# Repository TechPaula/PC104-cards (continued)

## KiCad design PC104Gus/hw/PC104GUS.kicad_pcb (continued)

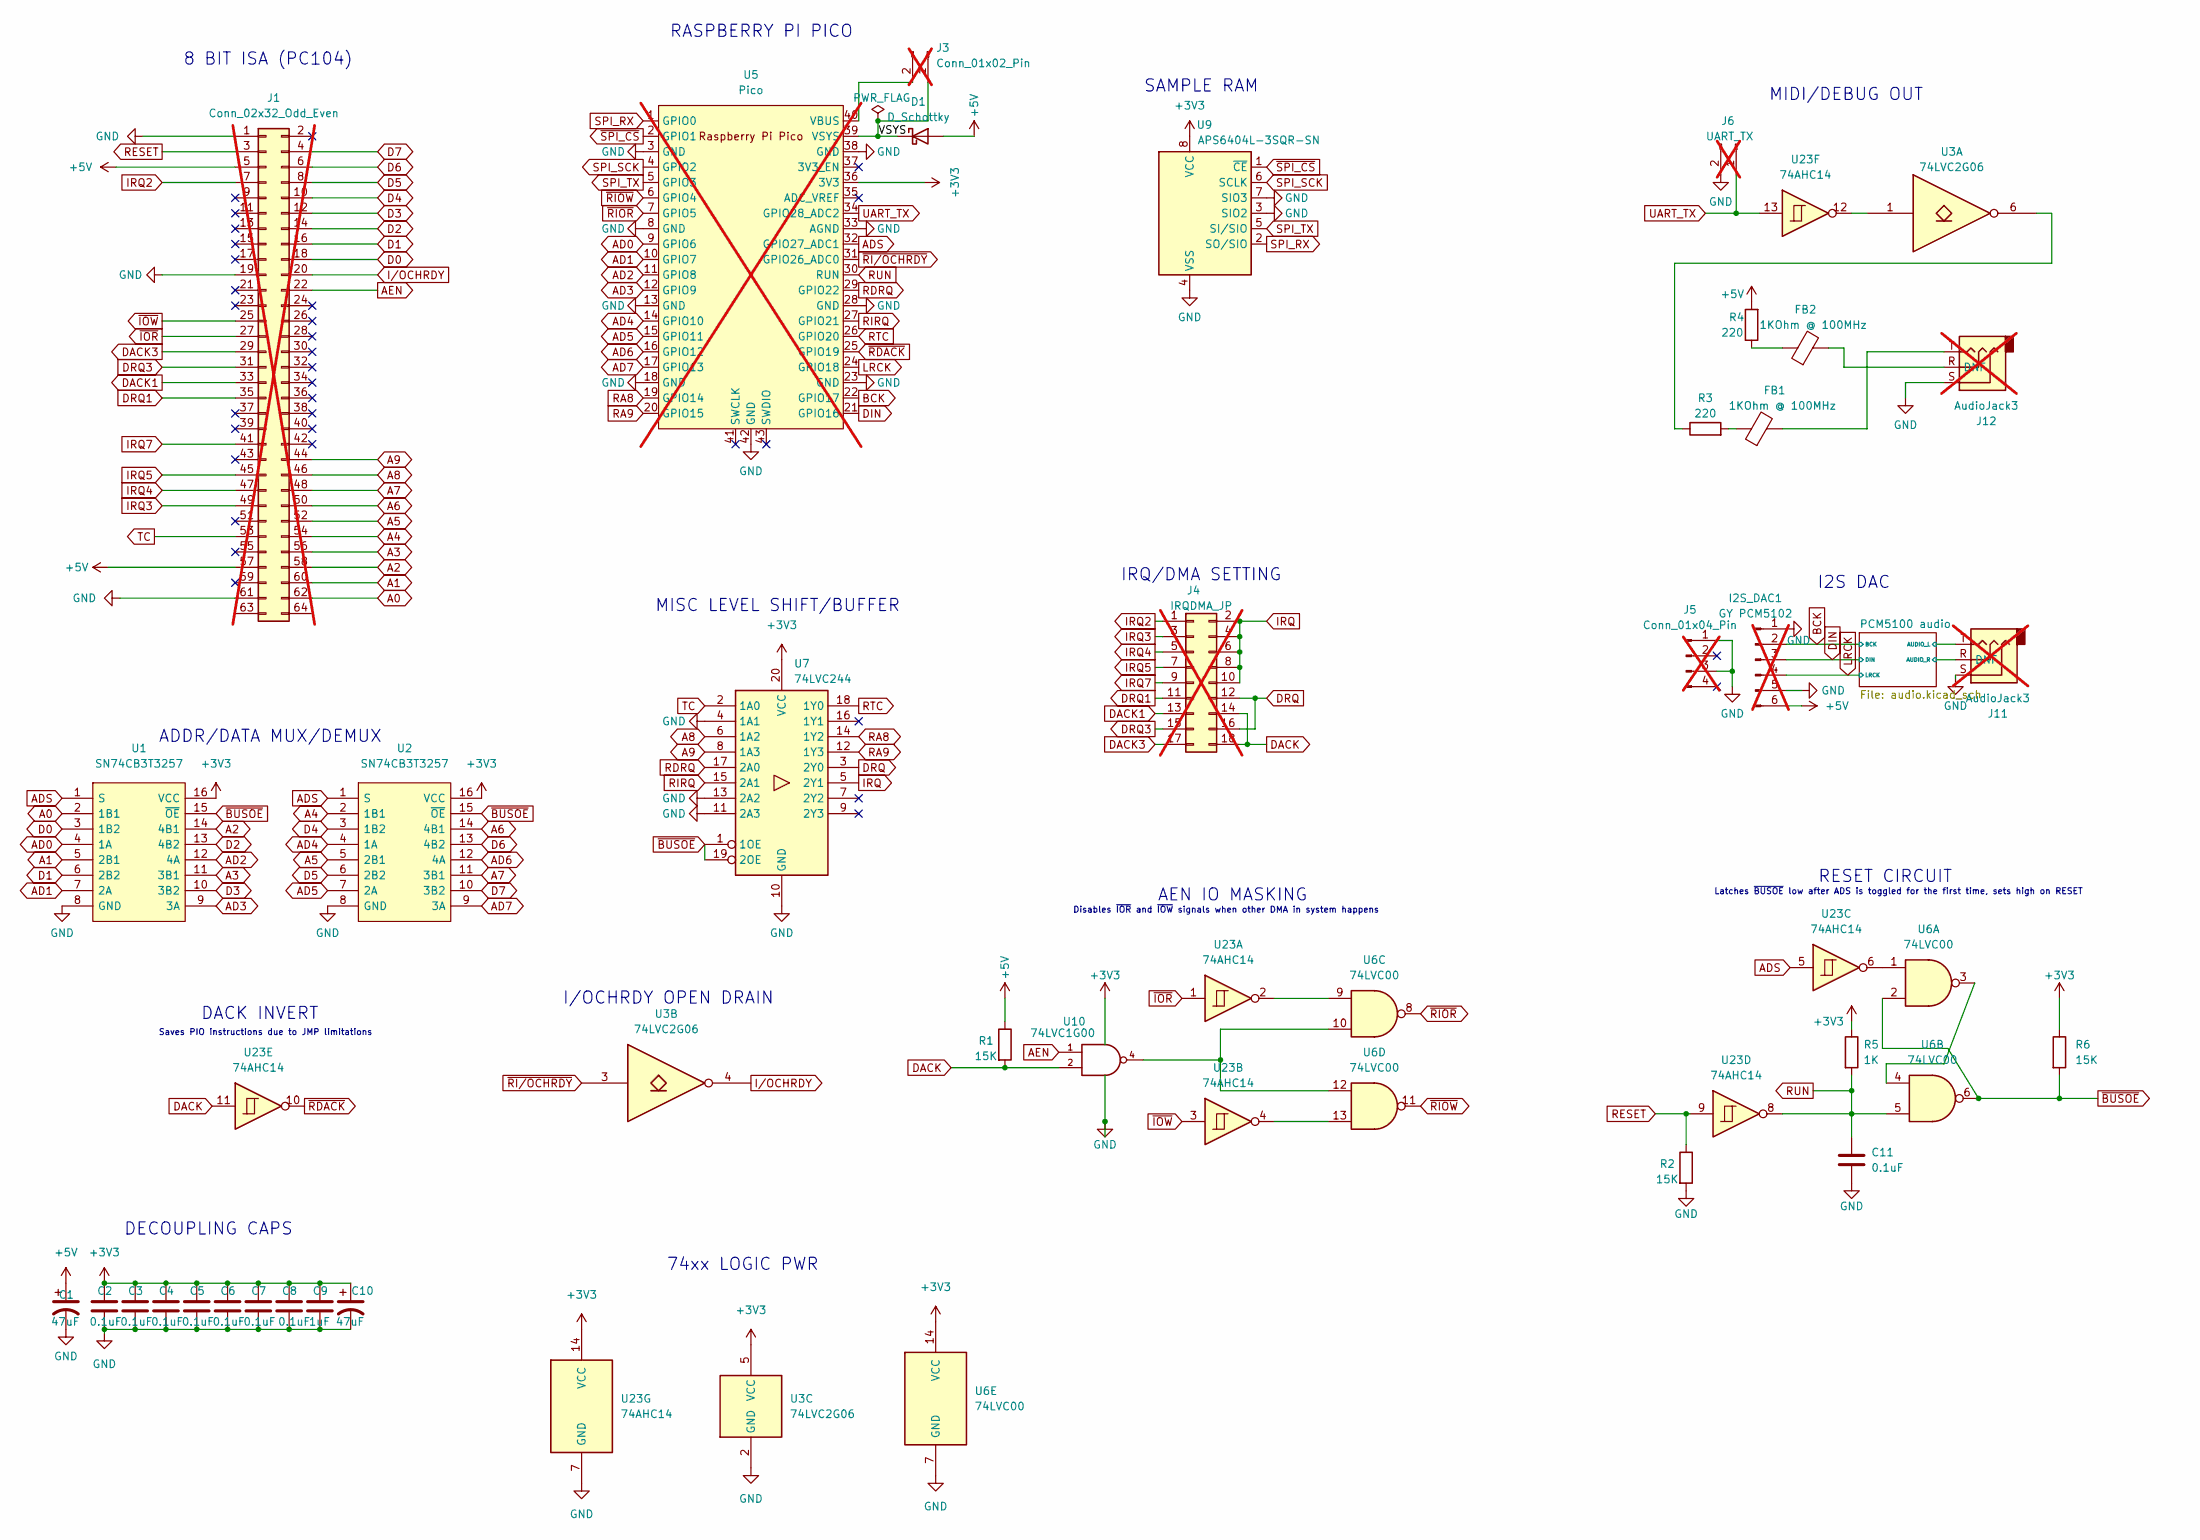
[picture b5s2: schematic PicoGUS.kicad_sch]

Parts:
C1, C10: 47uF; C_1206_3216Metric; LCSC C96123
C2, C3, C4, C5, C6, C7, C8, C11: 0.1uF; C_0805_2012Metric; LCSC C49678
C9: 1uF; C_0805_2012Metric; LCSC C28323
D1: D_Schottky; D_SOD-123; LCSC C8598
FB1, FB2: 1KOhm @ 100MHz; L_0805_2012Metric; LCSC C85835
I2S_DAC1: GY PCM5102; PinHeader_1x06_P2.54mm_Vertical; LCSC DNF; not fitted
J1: Conn_02x32_Odd_Even; PinSocket_2x32_P2.54mm_Vertical; LCSC DNF; not fitted
J3: Conn_01x02_Pin; PinHeader_1x02_P2.54mm_Vertical; LCSC DNF; not fitted
J4: IRQDMA_JP; PinHeader_2x09_P2.54mm_Vertical; LCSC DNF; not fitted
J5: Conn_01x04_Pin; PinHeader_1x04_P2.54mm_Vertical; LCSC DNF; not fitted
J6: UART_TX; PinHeader_1x02_P2.54mm_Vertical; LCSC DNF; not fitted
J11, J12: AudioJack3; Jack_3.5mm_CUI_SJ-3524-SMT_Horizontal; LCSC DNF; not fitted
R1, R2, R6: 15K; R_0805_2012Metric; LCSC C17475
R3, R4: 220; R_0805_2012Metric; LCSC C5120092
R5: 1K; R_0805_2012Metric; LCSC C17513
U1, U2: SN74CB3T3257; TSSOP-16_4.4x5mm_P0.65mm; Manufacturer_Part_Number 74FST3257DR2G; Mouser Part Number 863-74FST3257DR2G
U3: 74LVC2G06; SOT-23-6; LCSC C402162
U5: Pico; RPi_Pico_SMD_TH; LCSC DNF; not fitted
U6: 74LVC00; SO-14_3.9x8.65mm_P1.27mm; LCSC C526338
U7: 74LVC244; TSSOP-20_4.4x6.5mm_P0.65mm; LCSC C6079
U9: APS6404L-3SQR-SN; SOIC-8_3.9x4.9mm_P1.27mm; LCSC C139966
U10: 74LVC1G00; SOT-23-5; LCSC C7826
U23: 74AHC14; SO-14_3.9x8.65mm_P1.27mm; LCSC C5510

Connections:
+3V3: C2.1, C3.1, C4.1, C5.1, C6.1, C7.1, C8.1, C9.1, C10.1, R5.1, R6.1, U1.16 (VCC), U2.16 (VCC), U3.5 (VCC), U5.36 (3V3), U6.14 (VCC), U7.20 (VCC), U9.8 (VCC), U10.5 (VCC), U23.14 (VCC); also elsewhere on the board
+5V: C1.1, D1.2 (A), I2S_DAC1.6, J1.5, J1.57, R1.1, R4.2
/PicoGUS/PCM5100 audio/AUDIO_L: J11.T; also elsewhere on the board
/PicoGUS/PCM5100 audio/AUDIO_R: J11.R; also elsewhere on the board
/PicoGUS/VSYS: D1.1 (K), J3.1, U5.39 (VSYS)
A0: J1.62, U1.2 (1B1)
A1: J1.60, U1.5 (2B1)
A2: J1.58, U1.14 (4B1)
A3: J1.56, U1.11 (3B1)
A4: J1.54, U2.2 (1B1)
A5: J1.52, U2.5 (2B1)
A6: J1.50, U2.14 (4B1)
A7: J1.48, U2.11 (3B1)
A8: J1.46, U7.6 (1A2)
A9: J1.44, U7.8 (1A3)
AD0: U1.4 (1A), U5.9 (GPIO6)
AD1: U1.7 (2A), U5.10 (GPIO7)
AD2: U1.12 (4A), U5.11 (GPIO8)
AD3: U1.9 (3A), U5.12 (GPIO9)
AD4: U2.4 (1A), U5.14 (GPIO10)
AD5: U2.7 (2A), U5.15 (GPIO11)
AD6: U2.12 (4A), U5.16 (GPIO12)
AD7: U2.9 (3A), U5.17 (GPIO13)
ADS: U1.1 (S), U2.1 (S), U5.32 (GPIO27_ADC1), U23.5
AEN: J1.22, U10.1
BCK: I2S_DAC1.2, U5.22 (GPIO17); also elsewhere on the board
D0: J1.18, U1.3 (1B2)
D1: J1.16, U1.6 (2B2)
D2: J1.14, U1.13 (4B2)
D3: J1.12, U1.10 (3B2)
D4: J1.10, U2.3 (1B2)
D5: J1.8, U2.6 (2B2)
D6: J1.6, U2.13 (4B2)
D7: J1.4, U2.10 (3B2)
DACK: J4.14, J4.18, R1.2, U10.2, U23.11
DACK1: J1.33, J4.13
DACK3: J1.29, J4.17
DIN: I2S_DAC1.3, U5.21 (GPIO16); also elsewhere on the board
DRQ: J4.12, J4.16, U7.3 (2Y0)
DRQ1: J1.35, J4.11
DRQ3: J1.31, J4.15
GND: C1.2, C2.2, C3.2, C4.2, C5.2, C6.2, C7.2, C8.2, C9.2, C10.2, C11.2, I2S_DAC1.1, I2S_DAC1.5, J1.1, J1.19, J1.61, J5.1, J5.3, J6.2, J11.S, J12.S, R2.2, U1.8 (GND), U2.8 (GND), U3.2 (GND), U5.3 (GND), U5.8 (GND), U5.13 (GND), U5.18 (GND), U5.23 (GND), U5.28 (GND), U5.33 (AGND), U5.38 (GND), U5.42 (GND), U6.7 (GND), U7.4 (1A1), U7.10 (GND), U7.11 (2A3), U7.13 (2A2), U9.3 (SIO2), U9.4 (VSS), U9.7 (SIO3), U10.3 (GND), U23.7 (GND); also elsewhere on the board
IRQ: J4.2, J4.4, J4.6, J4.8, J4.10, U7.5 (2Y1)
IRQ2: J1.7, J4.1
IRQ3: J1.49, J4.3
IRQ4: J1.47, J4.5
IRQ5: J1.45, J4.7
IRQ7: J1.41, J4.9
I/OCHRDY: J1.20, U3.4
LRCK: I2S_DAC1.4, U5.24 (GPIO18); also elsewhere on the board
unnamed: FB1.1, R3.2
unnamed: FB1.2, J12.T
unnamed: FB2.1, R4.1
unnamed: FB2.2, J12.R
unnamed: J3.2, U5.40 (VBUS)
unnamed: R3.1, U3.6
unnamed: U6.3, U6.4
unnamed: U6.10, U6.12, U10.4
unnamed: U6.9, U23.2
unnamed: U6.13, U23.4
unnamed: U6.1, U23.6
unnamed: U3.1, U23.12
RA8: U5.19 (GPIO14), U7.14 (1Y2)
RA9: U5.20 (GPIO15), U7.12 (1Y3)
RDRQ: U5.29 (GPIO22), U7.17 (2A0)
RESET: J1.3, R2.1, U23.9
RIRQ: U5.27 (GPIO21), U7.15 (2A1)
RTC: U5.26 (GPIO20), U7.18 (1Y0)
RUN: C11.1, R5.2, U5.30 (RUN), U6.5, U23.8
SPI_RX: U5.1 (GPIO0), U9.2 (SO/SIO)
SPI_SCK: U5.4 (GPIO2), U9.6 (SCLK)
SPI_TX: U5.5 (GPIO3), U9.5 (SI/SIO)
TC: J1.53, U7.2 (1A0)
UART_TX: J6.1, U5.34 (GPIO28_ADC2), U23.13
~BUSOE: R6.2, U1.15 (~OE), U2.15 (~OE), U6.2, U6.6, U7.1 (1OE), U7.19 (2OE)
~IOR: J1.27, U23.1
~IOW: J1.25, U23.3
~RDACK: U5.25 (GPIO19), U23.10
~RIOR: U5.7 (GPIO5), U6.8
~RIOW: U5.6 (GPIO4), U6.11
~RI/OCHRDY: U3.3, U5.31 (GPIO26_ADC0)
~SPI_CS: U5.2 (GPIO1), U9.1 (~CE)

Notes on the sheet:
Saves PIO instructions due to JMP limitations
DECOUPLING CAPS
I2S DAC
Disables ~{IOR} and ~{IOW} signals when other DMA in system happens
Latches ~{BUSOE} low after ADS is toggled for the first time, sets high on RESET
MIDI/DEBUG OUT
MISC LEVEL SHIFT/BUFFER
IRQ/DMA SETTING
DACK INVERT
ADDR/DATA MUX/DEMUX
SAMPLE RAM
8 BIT ISA (PC104)
AEN IO MASKING
RASPBERRY PI PICO
RESET CIRCUIT
I/OCHRDY OPEN DRAIN
74xx LOGIC PWR

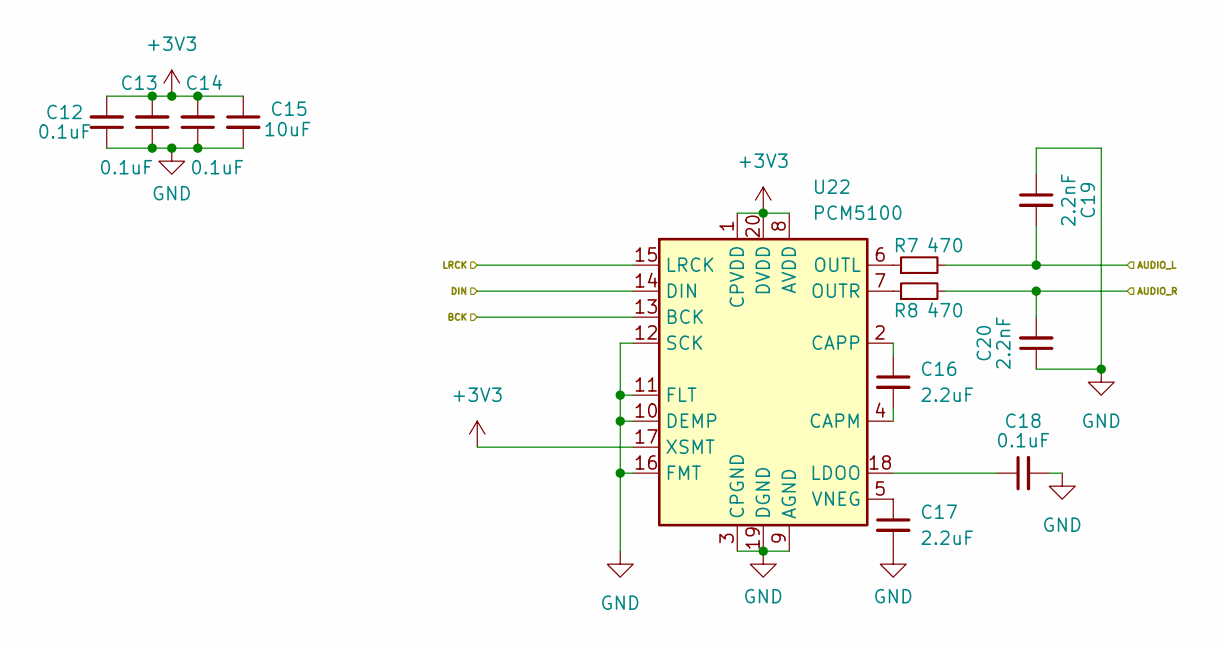
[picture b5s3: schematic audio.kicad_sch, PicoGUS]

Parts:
C12, C13, C14, C18: 0.1uF; C_0805_2012Metric; LCSC C49678
C15: 10uF; C_0805_2012Metric; LCSC C15850
C16, C17: 2.2uF; C_0805_2012Metric; LCSC C377773
C19, C20: 2.2nF; C_0805_2012Metric; LCSC C28260
R7, R8: 470; R_0805_2012Metric; LCSC C17710
U22: PCM5100; TSSOP-20_4.4x6.5mm_P0.65mm; LCSC C131154

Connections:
+3V3: C12.2, C13.2, C14.2, C15.1, U22.1 (CPVDD), U22.8 (AVDD), U22.17 (XSMT), U22.20 (DVDD); also elsewhere on the board
/PicoGUS/PCM5100 audio/AUDIO_L: C19.2, R7.2; also elsewhere on the board
/PicoGUS/PCM5100 audio/AUDIO_R: C20.2, R8.2; also elsewhere on the board
BCK: U22.13 (BCK); also elsewhere on the board
DIN: U22.14 (DIN); also elsewhere on the board
GND: C12.1, C13.1, C14.1, C15.2, C17.2, C18.2, C19.1, C20.1, U22.3 (CPGND), U22.9 (AGND), U22.10 (DEMP), U22.11 (FLT), U22.12 (SCK), U22.16 (FMT), U22.19 (DGND); also elsewhere on the board
LRCK: U22.15 (LRCK); also elsewhere on the board
unnamed: C16.2, U22.4 (CAPM)
unnamed: C16.1, U22.2 (CAPP)
unnamed: C18.1, U22.18 (LDOO)
unnamed: R7.1, U22.6 (OUTL)
unnamed: R8.1, U22.7 (OUTR)
unnamed: C17.1, U22.5 (VNEG)

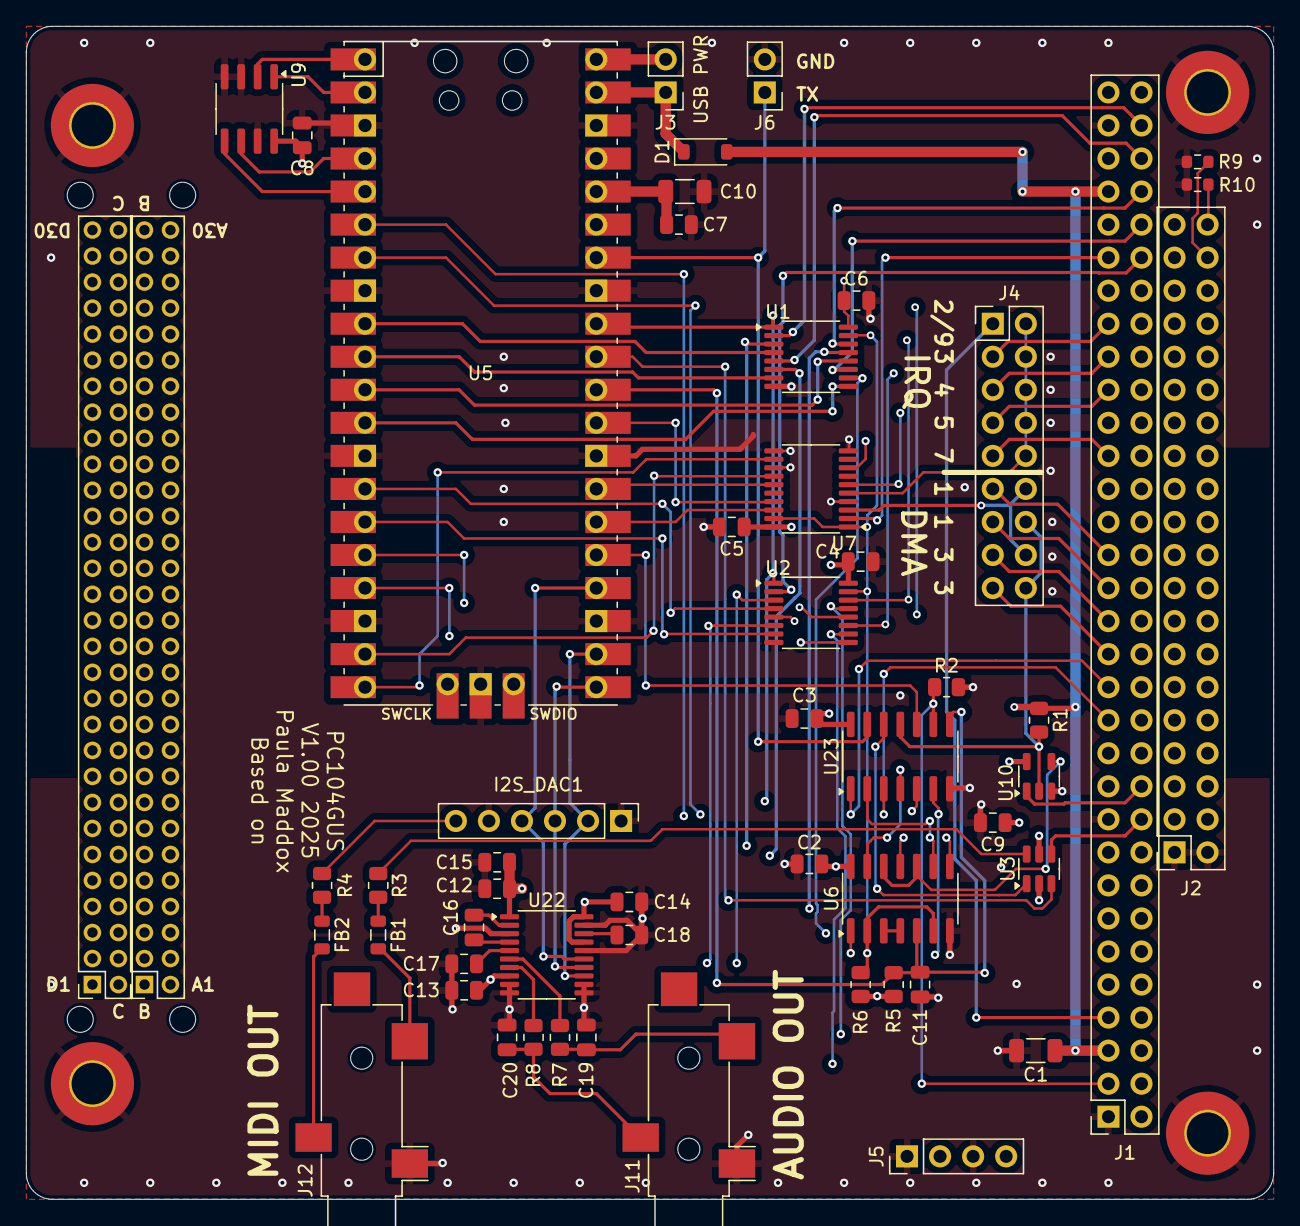
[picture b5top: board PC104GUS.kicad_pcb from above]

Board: 4 copper layers, 95.9 x 90.2 mm, 63 parts (1 on the bottom side), 90 nets.

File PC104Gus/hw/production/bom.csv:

Designator,Footprint,Quantity,Value,LCSC Part #
"C1, C10",1206,2,47uF,C96123
"C11, C12, C13, C14, C18, C2, C3, C4, C5, C6, C7, C8",0805,12,0.1uF,C49678
C15,0805,1,10uF,C15850
"C16, C17",0805,2,2.2uF,C377773
"C19, C20",0805,2,2.2nF,C28260
C9,0805,1,1uF,C28323
D1,D_SOD-123,1,D_Schottky,C8598
"FB1, FB2",0805,2,1KOhm @ 100MHz,C85835
FOX1,Fox_avatar_18mm,1,SYM_Flash_Large,DNF
"H10, H7, H8, H9",MountingHole_2mm,4,MountingHole,DNF
"H3, H4, H5, H6",MountingHole_3.2mm_M3_Pad_TopBottom,4,MountingHole_Pad,DNF
I2S_DAC1,PinHeader_1x06_P2.54mm_Vertical,1,GY PCM5102,DNF
J1,PinSocket_2x32_P2.54mm_Vertical,1,Conn_02x32_Odd_Even,DNF
"J10, J9",PinSocket_2x30_P2.00mm_Vertical,2,Conn_02x30_Row_Letter_First,DNF
"J11, J12",Jack_3.5mm_CUI_SJ-3524-SMT_Horizontal,2,AudioJack3,DNF
J2,PinSocket_2x20_P2.54mm_Vertical,1,Conn_02x20_Odd_Even,DNF
J3,PinHeader_1x02_P2.54mm_Vertical,1,Conn_01x02_Pin,DNF
J4,PinHeader_2x09_P2.54mm_Vertical,1,IRQDMA_JP,DNF
J5,PinHeader_1x04_P2.54mm_Vertical,1,Conn_01x04_Pin,DNF
J6,PinHeader_1x02_P2.54mm_Vertical,1,UART_TX,DNF
"R1, R2, R6",0805,3,15K,C17475
"R10, R9",0603,2,0R,DNF
"R3, R4",0805,2,220,C5120092
R5,0805,1,1K,C17513
"R7, R8",0805,2,470,C17710
"U1, U2",TSSOP-16_4.4x5mm_P0.65mm,2,SN74CB3T3257,C544573
U10,SOT-23-5,1,74LVC1G00,C7826
U22,TSSOP-20_4.4x6.5mm_P0.65mm,1,PCM5100,C131154
U23,SO-14_3.9x8.65mm_P1.27mm,1,74AHC14,C5510
U3,SOT-23-6,1,74LVC2G06,C402162
U5,RPi_Pico_SMD_TH,1,Pico,DNF
U6,SO-14_3.9x8.65mm_P1.27mm,1,74LVC00,C526338
U7,TSSOP-20_4.4x6.5mm_P0.65mm,1,74LVC244,C6079
U9,SOIC-8_3.9x4.9mm_P1.27mm,1,APS6404L-3SQR-SN,C139966

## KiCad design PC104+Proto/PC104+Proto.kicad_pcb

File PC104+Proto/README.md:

# PC104+ Proto card

This is PC104+ Protoboard, with power broken out and a bunch of uncommitted 0.1" spaced holes to solder dip sockets, etc too.

The PCI connector is not connected and is not needed, it is there so that should I get any PCI cards in the future I can use them on my system

## Update
2025-07-05 - Updated to revision 1.1, this is a four layer board and breaks out the J1 and J2 connectors to allow you to solder to the J1/J2 without preventing stacking. Board not yet built/tested
2025-06-22 - Board routed but NOT yet built/tested.

## License
None, feel free to use it, but I give no warranty.

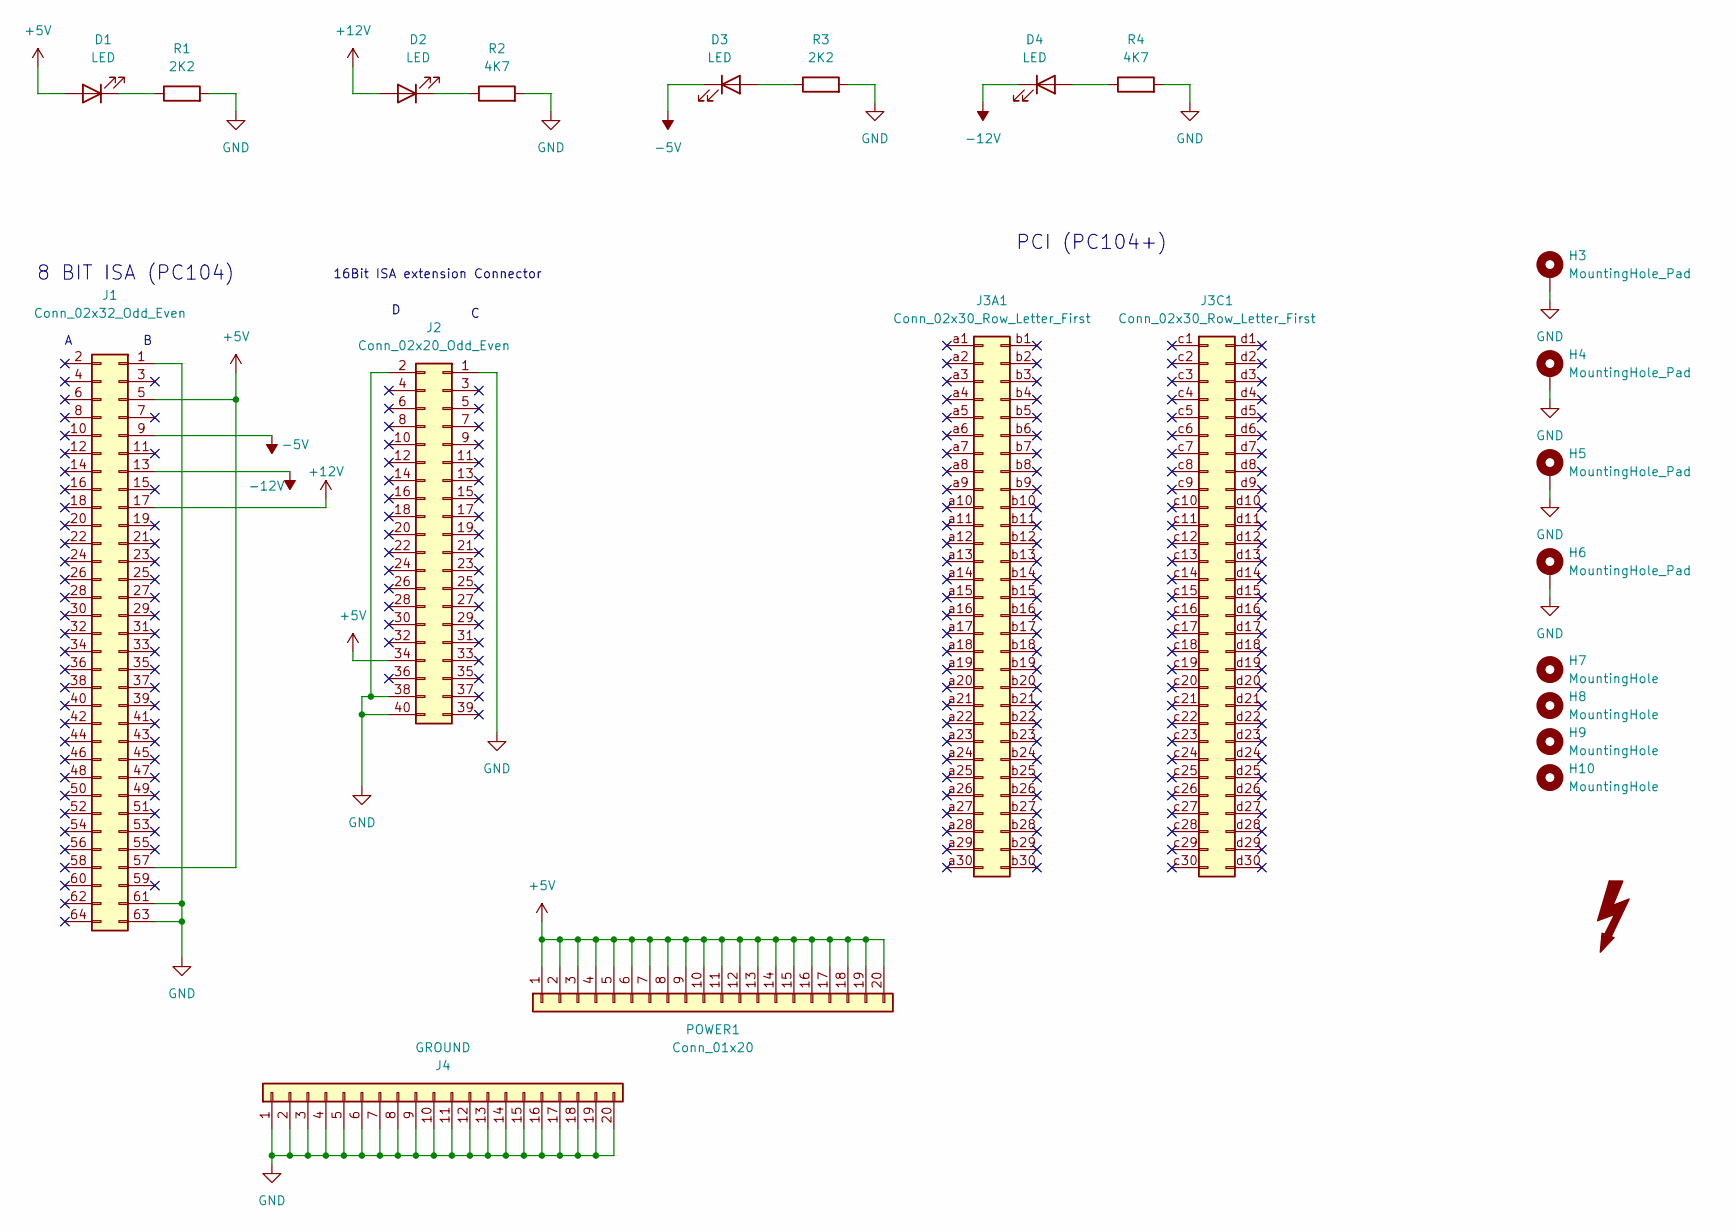
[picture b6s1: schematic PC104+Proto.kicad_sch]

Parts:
D1, D2, D3, D4: LED; LED_0603_1608Metric
FOX1: SYM_Flash_Large; Fox_avatar_18mm
H3, H4, H5, H6: MountingHole_Pad; MountingHole_3.2mm_M3_Pad_TopBottom
H7, H8, H9, H10: MountingHole; MountingHole_2mm
J1: Conn_02x32_Odd_Even; PinSocket_2x32_P2.54mm_Vertical
J2: Conn_02x20_Odd_Even; PinSocket_2x20_P2.54mm_Vertical
J3A1, J3C1: Conn_02x30_Row_Letter_First; PinSocket_2x30_P2.00mm_Vertical
J4: GROUND; PinSocket_1x20_P2.54mm_Vertical
POWER1: Conn_01x20; PinSocket_1x20_P2.54mm_Vertical
R1, R3: 2K2; R_0603_1608Metric
R2, R4: 4K7; R_0603_1608Metric

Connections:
+5V: D1.2 (A), J1.5, J1.57, J2.34, POWER1.1, POWER1.2, POWER1.3, POWER1.4, POWER1.5, POWER1.6, POWER1.7, POWER1.8, POWER1.9, POWER1.10, POWER1.11, POWER1.12, POWER1.13, POWER1.14, POWER1.15, POWER1.16, POWER1.17, POWER1.18, POWER1.19, POWER1.20
+12V: D2.2 (A), J1.17
-5V: D3.1 (K), J1.9
-12V: D4.1 (K), J1.13
GND: H3.1, H4.1, H5.1, H6.1, J1.1, J1.61, J1.63, J2.1, J2.2, J2.38, J2.40, J4.1, J4.2, J4.3, J4.4, J4.5, J4.6, J4.7, J4.8, J4.9, J4.10, J4.11, J4.12, J4.13, J4.14, J4.15, J4.16, J4.17, J4.18, J4.19, J4.20, R1.2, R2.2, R3.2, R4.2
unnamed: D1.1 (K), R1.1
unnamed: D2.1 (K), R2.1
unnamed: D3.2 (A), R3.1
unnamed: D4.2 (A), R4.1

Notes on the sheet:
8 BIT ISA (PC104)
PCI (PC104+)
16Bit ISA extension Connector

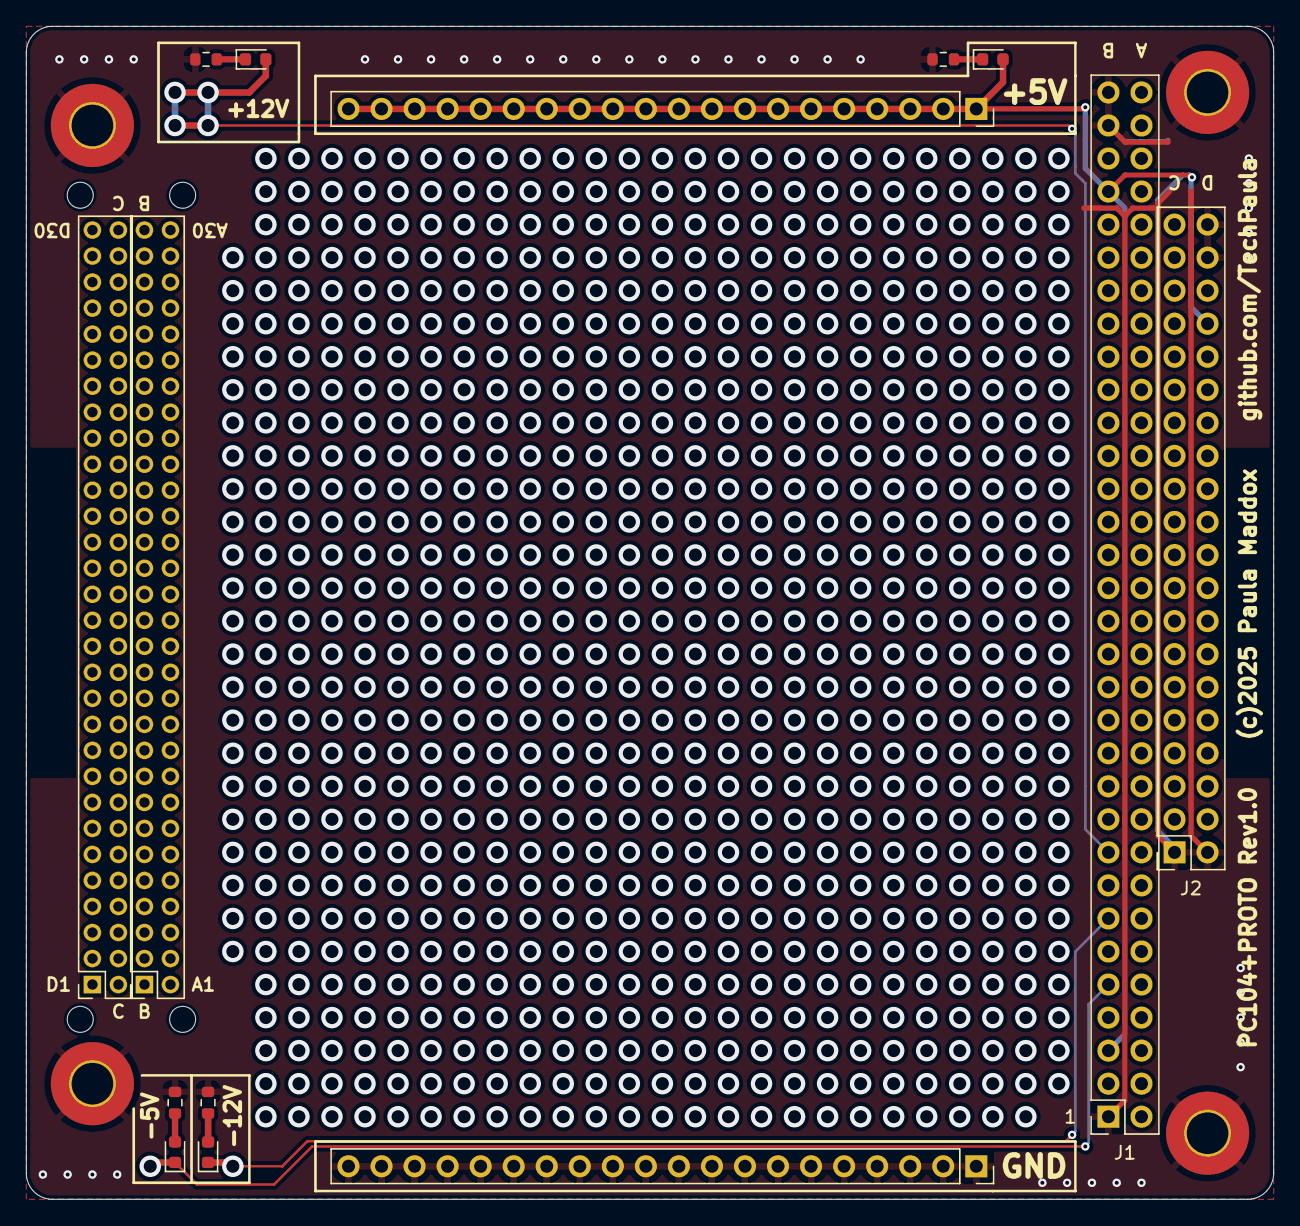
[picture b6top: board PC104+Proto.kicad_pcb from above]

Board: 2 copper layers, 95.9 x 90.2 mm, 23 parts (1 on the bottom side), 9 nets.

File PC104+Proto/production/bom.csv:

Designator,Footprint,Quantity,Value,LCSC Part #
"D1, D2, D3, D4",0603,4,LED,
FOX1,Fox_avatar_18mm,1,SYM_Flash_Large,
J1,PinSocket_2x32_P2.54mm_Vertical,1,Conn_02x32_Odd_Even,
J2,PinSocket_2x20_P2.54mm_Vertical,1,Conn_02x20_Odd_Even,
"J3A1, J3C1",PinSocket_2x30_P2.00mm_Vertical,2,Conn_02x30_Row_Letter_First,
J4,PinSocket_1x20_P2.54mm_Vertical,1,GROUND,
POWER1,PinSocket_1x20_P2.54mm_Vertical,1,Conn_01x20,
"R1, R3",0603,2,2K2,
"R2, R4",0603,2,4K7,

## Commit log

2025-06-20 Update README.md
    Added words
2025-06-20 Inital rename/commit
2025-06-20 Update README.md
    Corrected spelling
2025-06-20 Part position complete
    Added all parts, sorted part numbering and foot prints.
    Beginning routing
2025-06-21 Board routing complete
    DRC run, Need to update Schematic with parts from JLCPCB
2025-06-21 update README add pictures
2025-06-21 Update README.md
    Correct spelling...
2025-06-22 Initial version of PC104+Proto PCB
    Initial version of PC104+ProtoPCB
2025-06-22 Update README.md
    Added image
2025-07-04 PC104GUS production files
    Production files generated. This build worked!
2025-07-04 PC104GUS added actual image
2025-07-05 PC104 Transputer card
    Schematic design and PCB design
2025-07-05 Create README.md
    Created readme
2025-07-05 Update README.md
    remove link
2025-07-05 Updated .gitignore and added rev1.1 of Protoboard
2025-07-05 Added Rev 1.1 image
2025-07-06 Created a TRAM Model
2025-07-06 updated image of Transputer PC104 card
2025-07-06 Fixing a few things
    Fixed a couple of minor things with the schematic and board for both cards
    Also created Schematics
2025-07-06 Updated README and added image
2025-07-09 Fixed CPLD pinout
    Fixed the CPLD pin out which would never have worked with the previous version due to the PLCC and TQFP pinouts being different
2025-07-11 Fixed error with PCB, added CPLD files
    CPLD files tested on breadboard with a bunch of wires. PCB mistake fixed.
2025-07-12 Added extra jumpers to transputer board
    I also moved the downstream link to the same place as the upstream on the dual TRAM card.
2025-07-19 Board assembled, work on CPLD code
    I found a bunch of mistakes in the CPLD equations, it's still not quite right yet
2025-07-19 Update README.md
    fixed mistake in readme.
2025-07-29 Fixed bug in CPLD code
    Found yet another bug in the CPLD code and now my Qbasic program can read from a TRAM, write a 32bit value to TRAM and then read it back!!
    ISPY is VERY intermittant still
2025-09-07 Created C011 Link only PCB
    Created a new PCB with just the link adapter on it and extra signals to the CPLD to help with decoding.
2025-09-07 Added CPLD code for Link adapter
